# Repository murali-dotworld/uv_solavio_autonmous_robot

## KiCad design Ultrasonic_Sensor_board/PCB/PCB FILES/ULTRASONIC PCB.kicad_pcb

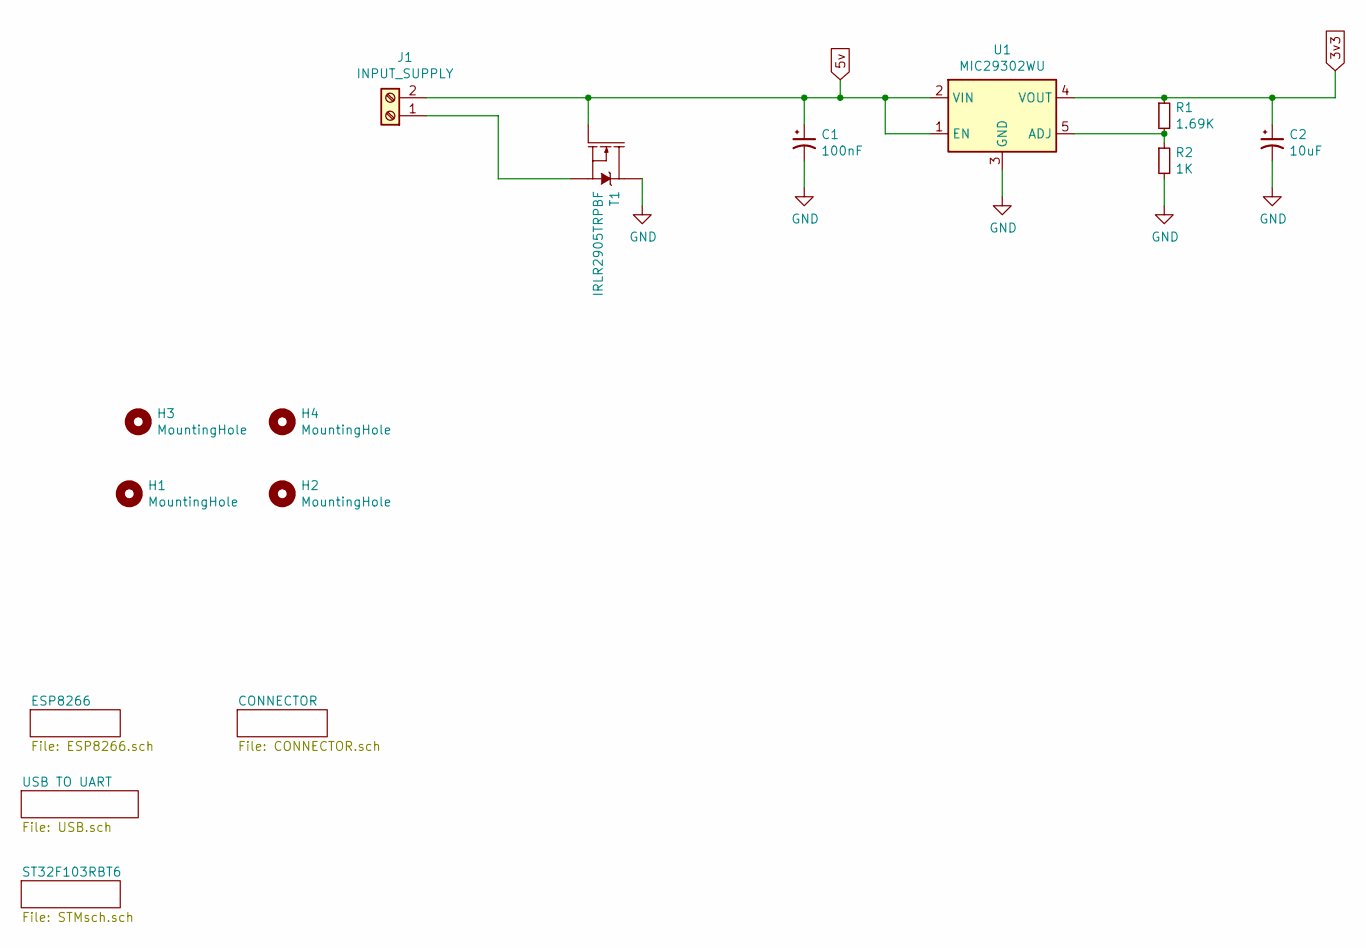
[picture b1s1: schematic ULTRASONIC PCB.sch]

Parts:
C1: 100nF; CP_Radial_D5.0mm_P2.00mm
C2: 10uF; CP_Radial_D5.0mm_P2.00mm
H1, H2, H3, H4: MountingHole; MountingHole_4.3mm_M4
J1: INPUT_SUPPLY; TerminalBlock_bornier-2_P5.08mm
R1: 1.69K; R_0805_2012Metric
R2: 1K; R_0805_2012Metric
T1: IRLR2905TRPBF; TO252-3
U1: MIC29302WU; TO-263-5_TabPin3

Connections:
3v3: C2.1, R1.1, U1.4 (VOUT); also elsewhere on the board
5v: C1.1, J1.2, T1.1, U1.1 (EN), U1.2 (VIN); also elsewhere on the board
GND: C1.2, C2.2, R2.2, T1.2, T1.PAD, U1.3 (GND); also elsewhere on the board
unnamed: J1.1, T1.3
unnamed: R1.2, R2.1, U1.5 (ADJ)

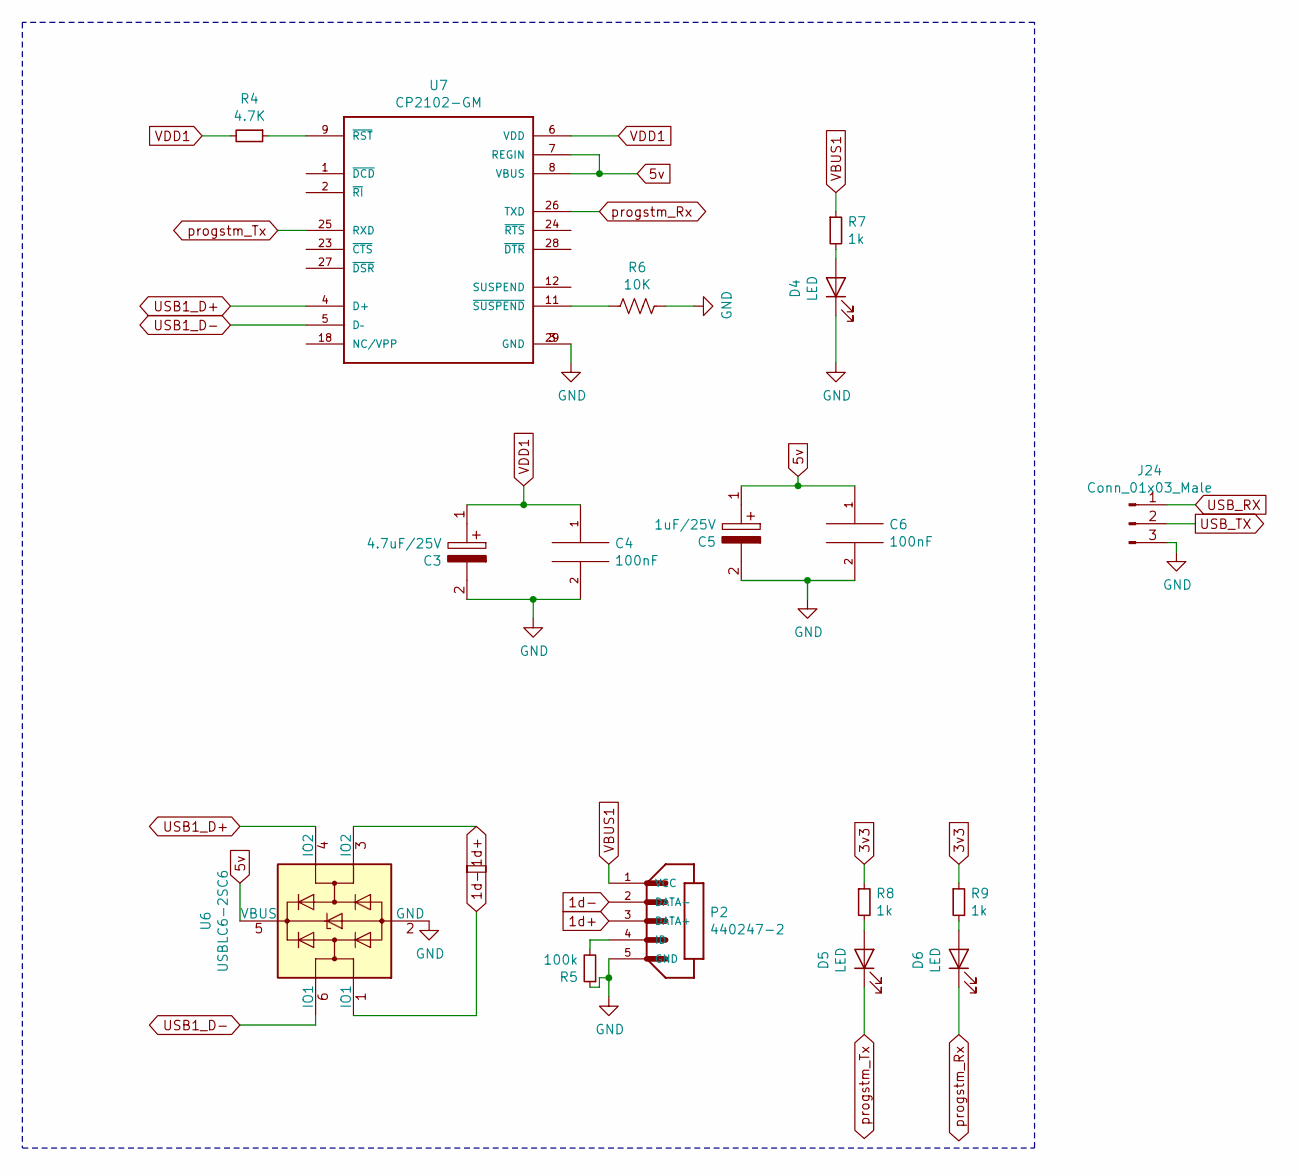
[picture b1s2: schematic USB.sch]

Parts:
C3: 4.7uF/25V; CP_EIA-3216-18_Kemet-A_Pad1.58x1.35mm_HandSolder; Manufacturer_Part_Number TAJA105M020RNJ; Mouser Part Number 581-TAJA105M020
C4, C6: 100nF; C_0805_2012Metric
C5: 1uF/25V; CP_EIA-3216-18_Kemet-A_Pad1.58x1.35mm_HandSolder; Manufacturer_Part_Number TAJA105M020RNJ; Mouser Part Number 581-TAJA105M020
D4, D5, D6: LED; LED_0805_2012Metric
J24: Conn_01x03_Male; PinHeader_1x03_P2.54mm_Vertical
P2: 440247-2; TE_440247-2
R4: 4.7K; R_0805_2012Metric
R5: 100k; R_0805_2012Metric
R6: 10K; R_0805_2012Metric
R7, R8, R9: 1k; R_0805_2012Metric
U6: USBLC6-2SC6; SOT-23-6
U7: CP2102-GM; QFN50P500X500X100-29N

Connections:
1d+: P2.3 (DATA+), U6.3 (IO2)
1d-: P2.2 (DATA-), U6.1 (IO1)
3v3: R8.1, R9.1; also elsewhere on the board
5v: C5.1, C6.1, U6.5 (VBUS), U7.7 (REGIN), U7.8 (VBUS); also elsewhere on the board
GND: C3.2, C4.2, C5.2, C6.2, D4.1 (K), J24.3, P2.5 (GND), R5.1, R6.1, U6.2 (GND), U7.3 (GND), U7.29 (GND); also elsewhere on the board
unnamed: D4.2 (A), R7.2
unnamed: D5.2 (A), R8.2
unnamed: D6.2 (A), R9.2
unnamed: P2.4 (ID), R5.2
unnamed: R4.1, U7.9 (~RST~)
unnamed: R6.2, U7.11 (~SUSPEND~)
USB1_D+: U6.4 (IO2), U7.4 (D+)
USB1_D-: U6.6 (IO1), U7.5 (D–)
USB_RX: J24.1; also elsewhere on the board
USB_TX: J24.2; also elsewhere on the board
VBUS1: P2.1 (VCC), R7.1
VDD1: C3.1, C4.1, R4.2, U7.6 (VDD)
progstm_Rx: D6.1 (K), U7.26 (TXD); also elsewhere on the board
progstm_Tx: D5.1 (K), U7.25 (RXD); also elsewhere on the board

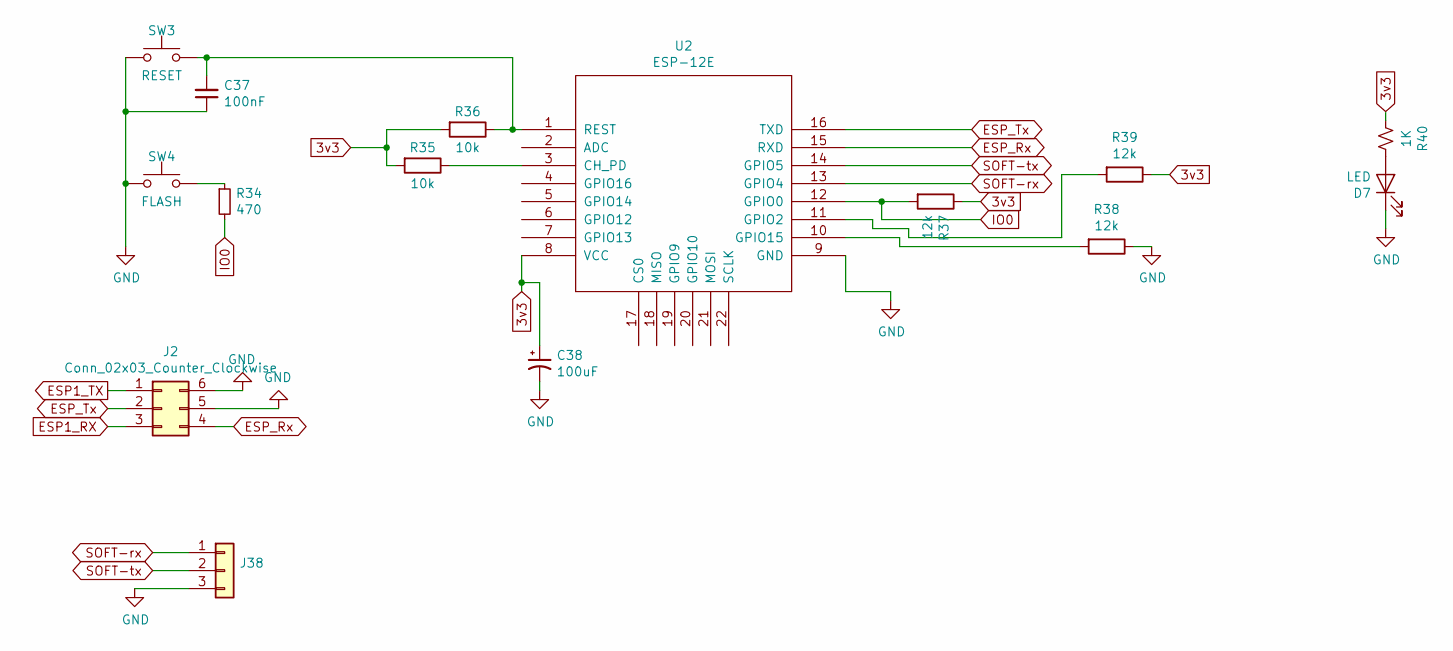
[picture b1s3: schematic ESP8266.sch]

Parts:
C37: 100nF; C_0805_2012Metric
C38: 100uF; CP_EIA-3216-18_Kemet-A_Pad1.58x1.35mm_HandSolder
D7: LED; LED_0805_2012Metric
J2: Conn_02x03_Counter_Clockwise; PinHeader_2x03_P2.54mm_Vertical
J38: Conn_01x03; PinHeader_1x03_P2.54mm_Vertical
R34: 470; R_0805_2012Metric
R35, R36: 10k; R_0805_2012Metric
R37, R38, R39: 12k; R_0805_2012Metric
R40: 1K; R_0805_2012Metric
SW3: RESET; SW_SPST_EVPBF
SW4: FLASH; SW_SPST_EVPBF
U2: ESP-12E; ESP-12E_SMD

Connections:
3v3: C38.1, R35.2, R36.2, R37.1, R39.1, R40.2, U2.8 (VCC); also elsewhere on the board
ESP1_RX: J2.3; also elsewhere on the board
ESP1_TX: J2.1; also elsewhere on the board
ESP_Rx: J2.4, U2.15 (RXD)
ESP_Tx: J2.2, U2.16 (TXD)
GND: C37.1, C38.2, D7.1 (K), J2.5, J2.6, J38.3, R38.1, SW3.1, SW4.1, U2.9 (GND); also elsewhere on the board
IO0: R34.2, R37.2, U2.12 (GPIO0)
unnamed: C37.2, R36.1, SW3.2, U2.1 (REST)
unnamed: D7.2 (A), R40.1
unnamed: R34.1, SW4.2
unnamed: R35.1, U2.3 (CH_PD)
unnamed: R38.2, U2.10 (GPIO15)
unnamed: R39.2, U2.11 (GPIO2)
SOFT-rx: J38.1, U2.13 (GPIO4)
SOFT-tx: J38.2, U2.14 (GPIO5)

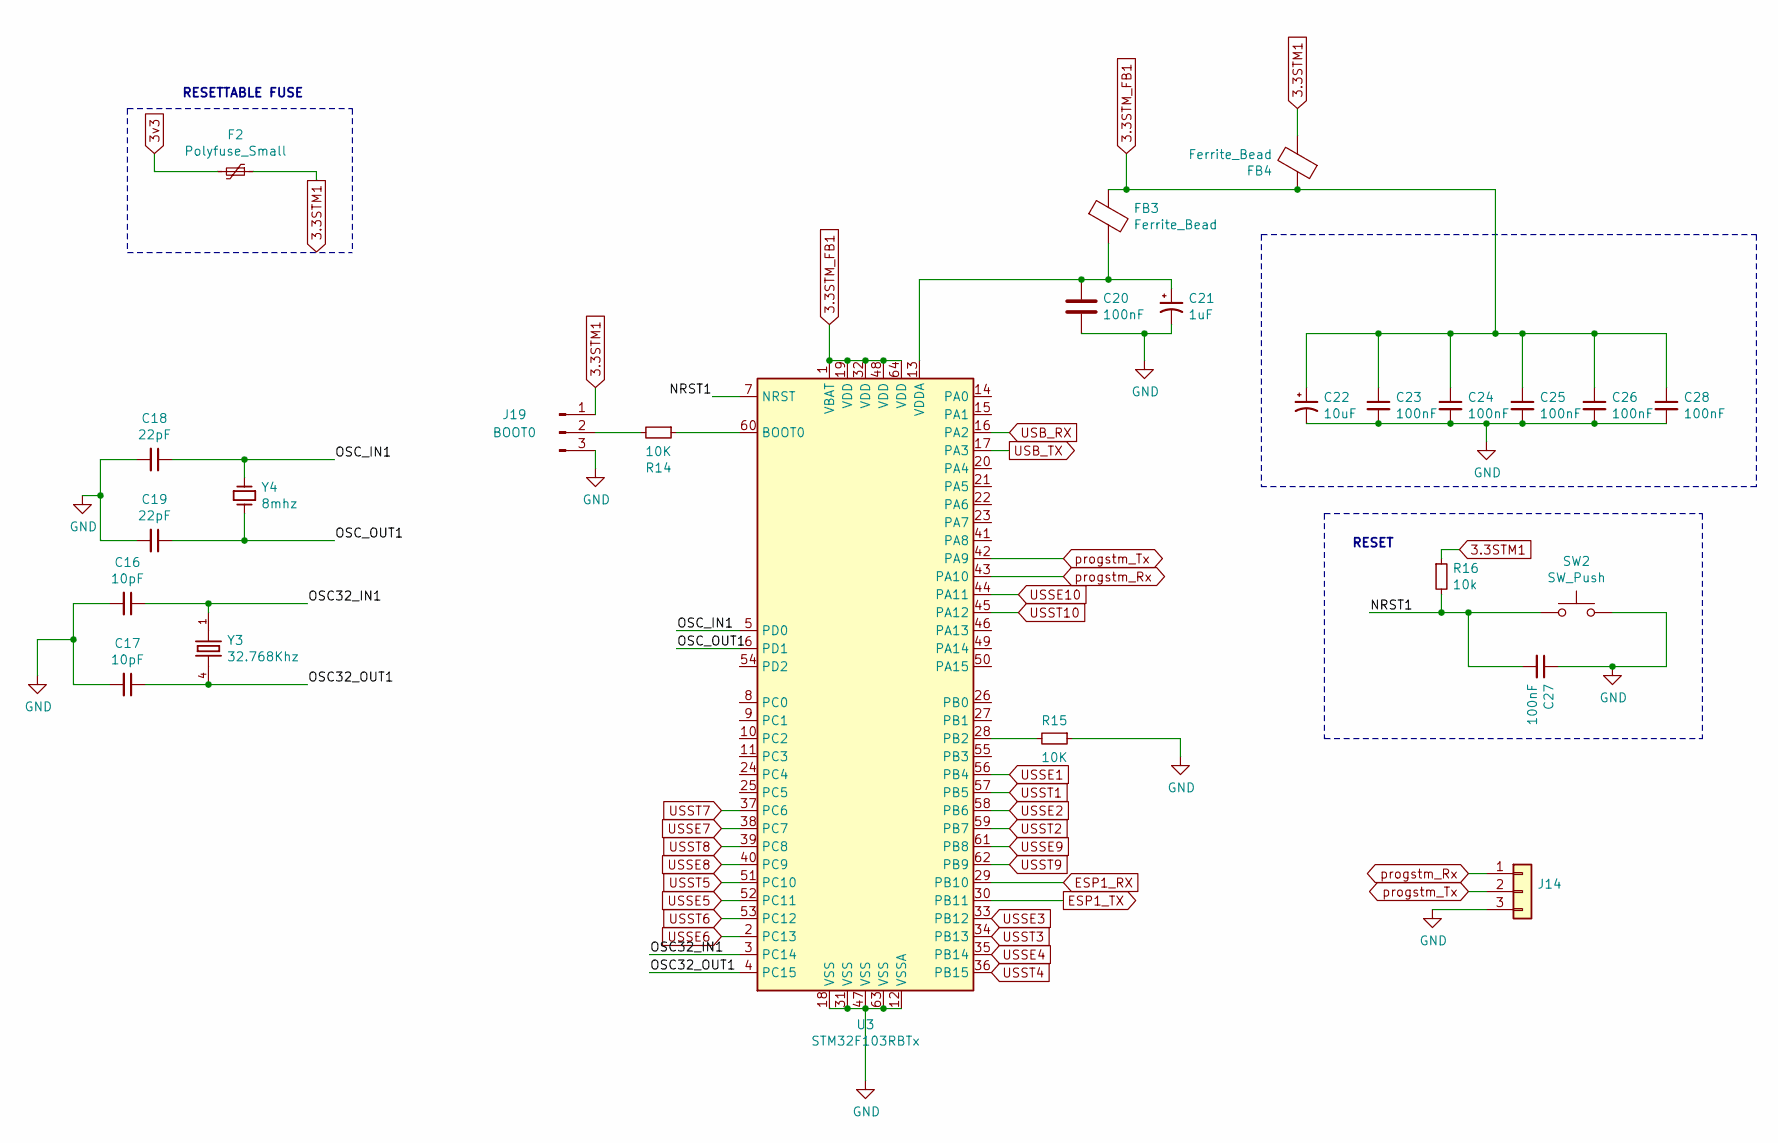
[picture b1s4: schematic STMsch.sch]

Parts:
C16, C17: 10pF; C_0805_2012Metric
C18, C19: 22pF; C_0805_2012Metric
C20, C23, C24, C25, C26, C27, C28: 100nF; C_0805_2012Metric
C21: 1uF; CP_EIA-3216-18_Kemet-A_Pad1.58x1.35mm_HandSolder
C22: 10uF; CP_EIA-3216-18_Kemet-A_Pad1.58x1.35mm_HandSolder
F2: Polyfuse_Small; C_1206_3216Metric
FB3, FB4: Ferrite_Bead; R_0805_2012Metric
J14: Conn_01x03; PinHeader_1x03_P2.54mm_Vertical
J19: BOOT0; PinHeader_1x03_P2.54mm_Vertical
R14, R15: 10K; R_0805_2012Metric
R16: 10k; R_0805_2012Metric
SW2: SW_Push; SW_SPST_EVPBF
U3: STM32F103RBTx; LQFP-64_10x10mm_P0.5mm
Y3: 32.768Khz; Crystal_SMD_SeikoEpson_MC306-4Pin_8.0x3.2mm
Y4: 8mhz; Crystal_HC49-U_Vertical

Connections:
3.3STM1: F2.1, FB4.2, J19.1, R16.1
3.3STM_FB1: C22.1, C23.1, C24.1, C25.1, C26.1, C28.1, FB3.1, FB4.1, U3.1 (VBAT), U3.19 (VDD), U3.32 (VDD), U3.48 (VDD), U3.64 (VDD)
3v3: F2.2; also elsewhere on the board
/ST32F103RBT6/NRST1: C27.2, R16.2, SW2.1, U3.7 (NRST)
/ST32F103RBT6/OSC32_IN1: C16.1, U3.3 (PC14), Y3.1
/ST32F103RBT6/OSC32_OUT1: C17.1, U3.4 (PC15), Y3.4
/ST32F103RBT6/OSC_IN1: C18.1, U3.5 (PD0), Y4.2
/ST32F103RBT6/OSC_OUT1: C19.1, U3.6 (PD1), Y4.1
ESP1_RX: U3.29 (PB10); also elsewhere on the board
ESP1_TX: U3.30 (PB11); also elsewhere on the board
GND: C16.2, C17.2, C18.2, C19.2, C20.2, C21.2, C22.2, C23.2, C24.2, C25.2, C26.2, C27.1, C28.2, J14.3, J19.3, R15.1, SW2.2, U3.12 (VSSA), U3.18 (VSS), U3.31 (VSS), U3.47 (VSS), U3.63 (VSS); also elsewhere on the board
unnamed: C20.1, C21.1, FB3.2, U3.13 (VDDA)
unnamed: J19.2, R14.2
unnamed: R14.1, U3.60 (BOOT0)
unnamed: R15.2, U3.28 (PB2)
USB_RX: U3.16 (PA2); also elsewhere on the board
USB_TX: U3.17 (PA3); also elsewhere on the board
USSE1: U3.56 (PB4); also elsewhere on the board
USSE2: U3.58 (PB6); also elsewhere on the board
USSE3: U3.33 (PB12); also elsewhere on the board
USSE4: U3.35 (PB14); also elsewhere on the board
USSE5: U3.52 (PC11); also elsewhere on the board
USSE6: U3.2 (PC13); also elsewhere on the board
USSE7: U3.38 (PC7); also elsewhere on the board
USSE8: U3.40 (PC9); also elsewhere on the board
USSE9: U3.61 (PB8); also elsewhere on the board
USSE10: U3.44 (PA11); also elsewhere on the board
USST1: U3.57 (PB5); also elsewhere on the board
USST2: U3.59 (PB7); also elsewhere on the board
USST3: U3.34 (PB13); also elsewhere on the board
USST4: U3.36 (PB15); also elsewhere on the board
USST5: U3.51 (PC10); also elsewhere on the board
USST6: U3.53 (PC12); also elsewhere on the board
USST7: U3.37 (PC6); also elsewhere on the board
USST8: U3.39 (PC8); also elsewhere on the board
USST9: U3.62 (PB9); also elsewhere on the board
USST10: U3.45 (PA12); also elsewhere on the board
progstm_Rx: J14.1, U3.43 (PA10); also elsewhere on the board
progstm_Tx: J14.2, U3.42 (PA9); also elsewhere on the board

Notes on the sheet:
RESETTABLE FUSE
RESET

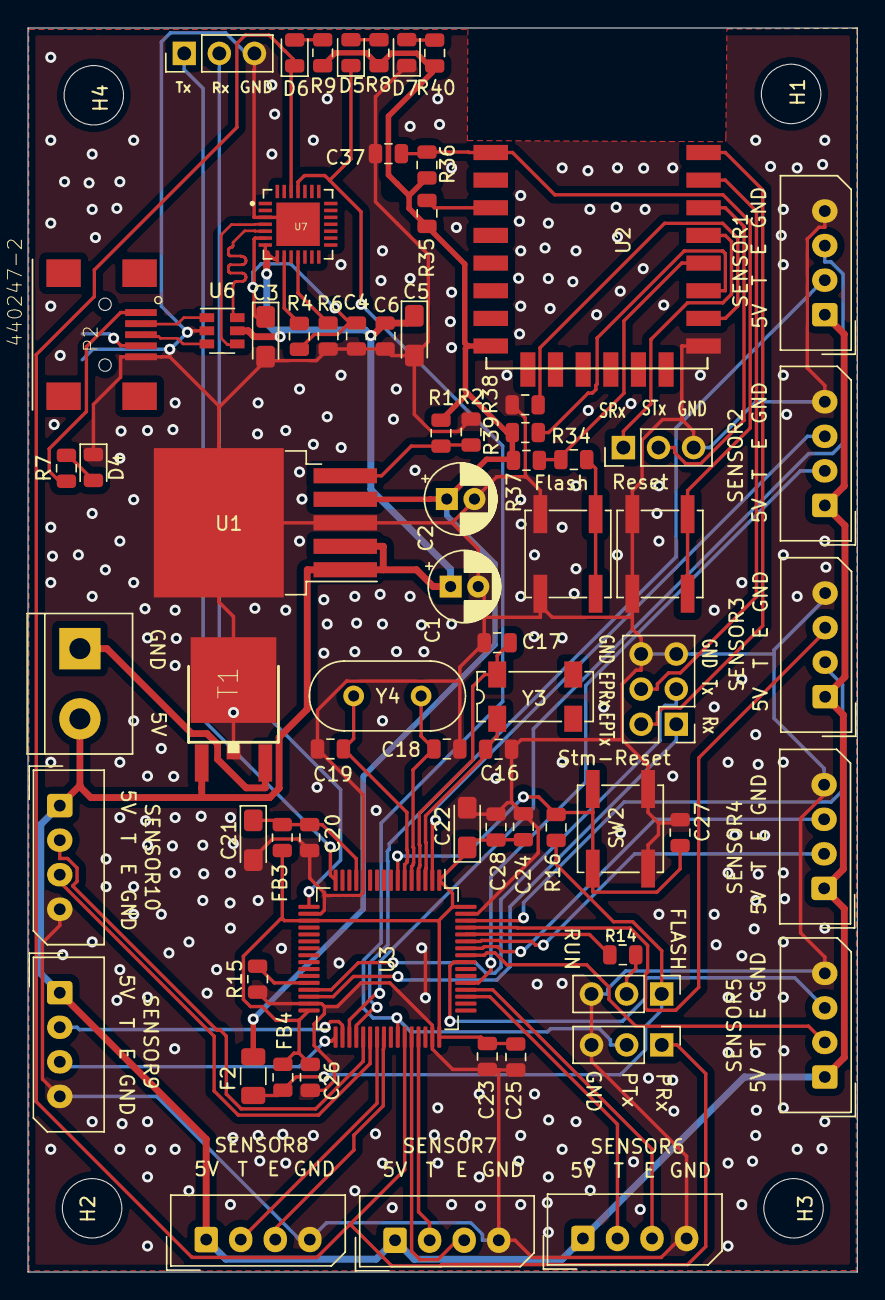
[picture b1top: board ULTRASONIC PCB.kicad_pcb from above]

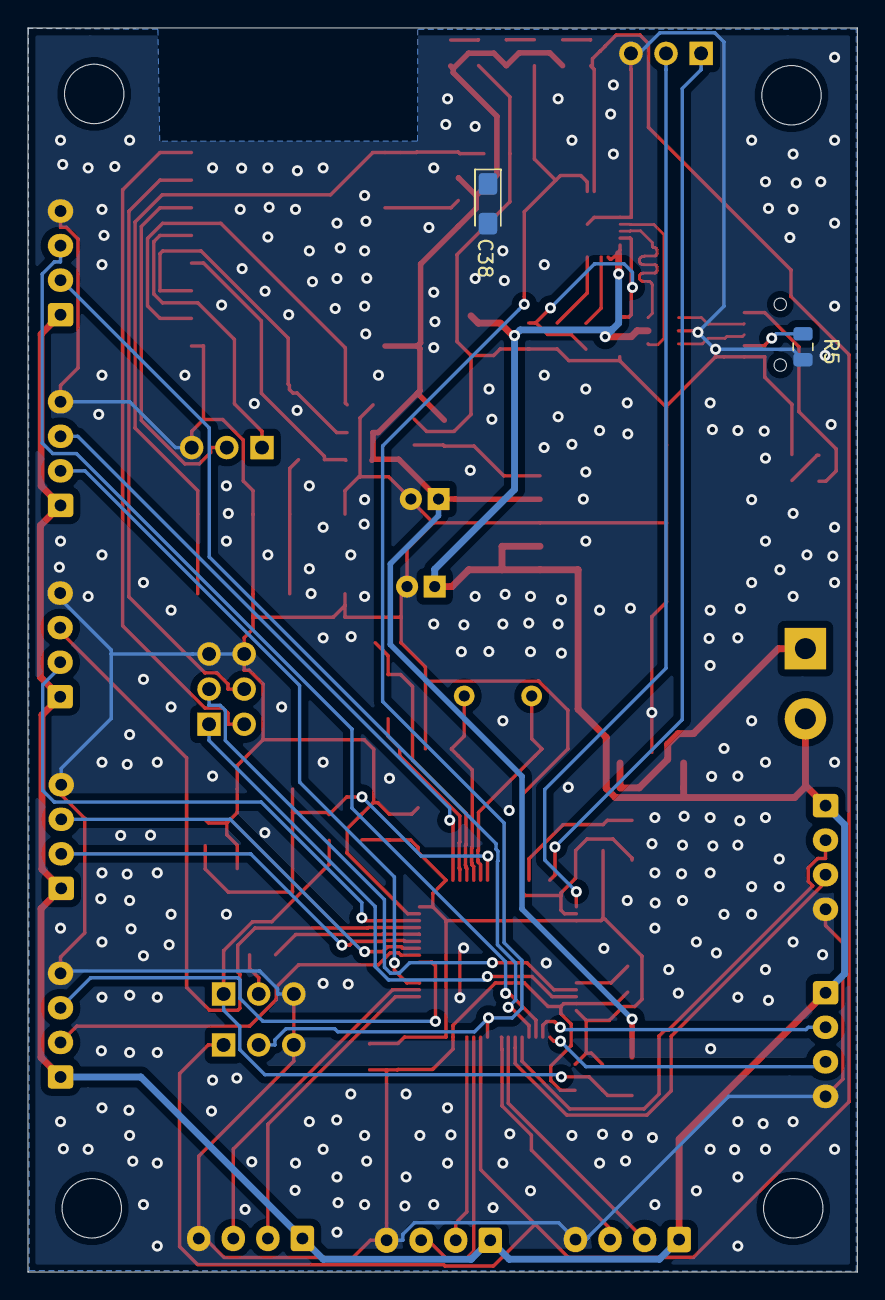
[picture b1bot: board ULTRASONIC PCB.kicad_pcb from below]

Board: 2 copper layers, 60.0 x 90.0 mm, 78 parts (2 on the bottom side), 65 nets.

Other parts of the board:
J3, J4, J5, J6, J7, J8, J9, J10, J11, J12: Screw_Terminal_01x04; Molex_SPOX_5267-04A_1x04_P2.50mm_Vertical

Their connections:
5v: J3.1, J4.1, J5.1, J6.1, J7.1, J8.1, J9.1, J10.1, J11.1, J12.1; also elsewhere on the board
GND: J3.4, J4.4, J5.4, J6.4, J7.4, J8.4, J9.4, J10.4, J11.4, J12.4; also elsewhere on the board
USSE1: J7.3; also elsewhere on the board
USSE2: J8.3; also elsewhere on the board
USSE3: J11.3; also elsewhere on the board
USSE4: J12.3; also elsewhere on the board
USSE5: J5.3; also elsewhere on the board
USSE6: J9.3; also elsewhere on the board
USSE7: J6.3; also elsewhere on the board
USSE8: J10.3; also elsewhere on the board
USSE9: J3.3; also elsewhere on the board
USSE10: J4.3; also elsewhere on the board
USST1: J7.2; also elsewhere on the board
USST2: J8.2; also elsewhere on the board
USST3: J11.2; also elsewhere on the board
USST4: J12.2; also elsewhere on the board
USST5: J5.2; also elsewhere on the board
USST6: J9.2; also elsewhere on the board
USST7: J6.2; also elsewhere on the board
USST8: J10.2; also elsewhere on the board
USST9: J3.2; also elsewhere on the board
USST10: J4.2; also elsewhere on the board

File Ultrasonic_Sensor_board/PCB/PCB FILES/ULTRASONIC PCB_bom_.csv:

Component,Description,Part,References,Value,Footprint,Quantity Per PCB,Datasheet,Mouser Price/Stock,Mouser Part Number,Manufacturer_Name,Height,RS Price/Stock,RS Part Number,Manufacturer_Part_Number,Field10,Field8,Field9,Field4,Field7,Field6,Field5
1,"Unpolarized capacitor, small symbol",C_Small,C16 C17,10pF,C_0805_2012Metric,2,~,,,,,,,,,,,,,,
2,"Unpolarized capacitor, small symbol",C_Small,C18 C19,22pF,C_0805_2012Metric,2,~,,,,,,,,,,,,,,
3,"Polarized capacitor, small US symbol",CP1_Small,C1,100nF,CP_Radial_D5.0mm_P2.00mm,1,~,,,,,,,,,,,,,,
4,Unpolarized capacitor,C,C20 C23 C24 C25 C26 C27 C28 C37,100nF,C_0805_2012Metric,8,~,,,,,,,,,,,,,,
5,Capacitor symbol for simulation only,C,C4 C6,100nF,C_0805_2012Metric,2,~,,,,,,,,,,,,,,
6,"Polarized capacitor, small US symbol",CP1_Small,C21,1uF,CP_EIA-3216-18_Kemet-A_Pad1.58x1.35mm_HandSolder,1,~,,,,,,,,,,,,,,
7,"Polarized capacitor, small US symbol",CP1_Small,C2,10uF,CP_Radial_D5.0mm_P2.00mm,1,~,,,,,,,,,,,,,,
8,"Polarized capacitor, small US symbol",CP1_Small,C22,10uF,CP_EIA-3216-18_Kemet-A_Pad1.58x1.35mm_HandSolder,1,~,,,,,,,,,,,,,,
9,"Polarized capacitor, small US symbol",CP1_Small,C38,100uF,CP_EIA-3216-18_Kemet-A_Pad1.58x1.35mm_HandSolder,1,~,,,,,,,,,,,,,,
10,,TAJA105M020RNJ-c1206_smd_tantalum-Door_Locking-rescue,C5,1uF/25V,CP_EIA-3216-18_Kemet-A_Pad1.58x1.35mm_HandSolder,1,http://www.farnell.com/datasheets/1680476.pdf,https://www.mouser.com/Search/Refine.aspx?Keyword=581-TAJA105M020,581-TAJA105M020,AVX,1.8,http://uk.rs-online.com/web/p/products/1360152,1360152,TAJA105M020RNJ,,,,,,,
11,,TAJA105M020RNJ-c1206_smd_tantalum-Door_Locking-rescue,C3,4.7uF/25V,CP_EIA-3216-18_Kemet-A_Pad1.58x1.35mm_HandSolder,1,http://www.farnell.com/datasheets/1680476.pdf,https://www.mouser.com/Search/Refine.aspx?Keyword=581-TAJA105M020,581-TAJA105M020,AVX,1.8,http://uk.rs-online.com/web/p/products/1360152,1360152,TAJA105M020RNJ,,,,,,,
12,Light emitting diode,LED,D4 D5 D6 D7,LED,LED_0805_2012Metric,4,~,,,,,,,,,,,,,,
13,"Resettable fuse, polymeric positive temperature coefficient, small symbol",Polyfuse_Small,F2,Polyfuse_Small,C_1206_3216Metric,1,~,,,,,,,,,,,,,,
14,Ferrite bead,Ferrite_Bead,FB3 FB4,Ferrite_Bead,R_0805_2012Metric,2,~,,,,,,,,,,,,,,
15,"Generic connector, single row, 01x03, script generated (kicad-library-utils/schlib/autogen/connector/)",Conn_01x03_Male,J19 J24,BOOT0,PinHeader_1x03_P2.54mm_Vertical,2,~,,,,,,,,,,,,,,
16,"Generic connector, single row, 01x03, script generated (kicad-library-utils/schlib/autogen/connector/)",Conn_01x03,J14 J38,Conn_01x03,PinHeader_1x03_P2.54mm_Vertical,2,~,,,,,,,,,,,,,,
17,"Generic connector, double row, 02x03, counter clockwise pin numbering scheme (similar to DIP packge numbering), script generated (kicad-library-utils/schlib/autogen/connector/)",Conn_02x03_Counter_Clockwise,J2,Conn_02x03_Counter_Clockwise,PinHeader_2x03_P2.54mm_Vertical,1,~,,,,,,,,,,,,,,
18,"Generic screw terminal, single row, 01x02, script generated (kicad-library-utils/schlib/autogen/connector/)",Screw_Terminal_01x02,J1,INPUT_SUPPLY,TerminalBlock_bornier-2_P5.08mm,1,~,,,,,,,,,,,,,,
19,"Generic screw terminal, single row, 01x04, script generated (kicad-library-utils/schlib/autogen/connector/)",Screw_Terminal_01x04,J3 J4 J5 J6 J7 J8 J9 J10 J11 J12,Screw_Terminal_01x04,Molex_SPOX_5267-04A_1x04_P2.50mm_Vertical,10,~,,,,,,,,,,,,,,
20,,440247-2-USB_MINI_B-SNAPEDA-Door_Locking-rescue,P2,440247-2,TE_440247-2,1,TE Connectivity,,,,,,,,https://www.te.com/usa-en/product-440247-2.html?te_bu=Cor&te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,440247-2,None,None,Mini USB B Type RCPT,Unavailable,440247-2
21,"Resistor, small symbol",R_Small,R34,470,R_0805_2012Metric,1,~,,,,,,,,,,,,,,
22,"Resistor, small symbol",R_Small,R2 R7 R8 R9,1K,R_0805_2012Metric,4,~,,,,,,,,,,,,,,
23,,R_Small_US-Device-esp-max-rescue,R40,1K,R_0805_2012Metric,1,~,,,,,,,,,,,,,,
24,"Resistor, small symbol",R_Small,R1,1.69K,R_0805_2012Metric,1,~,,,,,,,,,,,,,,
25,"Resistor, small symbol",R_Small,R4,4.7K,R_0805_2012Metric,1,~,,,,,,,,,,,,,,
26,"Resistor, small symbol",R_Small,R14 R15 R16 R35 R36,10K,R_0805_2012Metric,5,~,,,,,,,,,,,,,,
27,"Resistor, US symbol",R_US,R6,10K,R_0805_2012Metric,1,~,,,,,,,,,,,,,,
28,Resistor,R,R37 R38 R39,12k,R_0805_2012Metric,3,~,,,,,,,,,,,,,,
29,"Resistor, small symbol",R_Small,R5,100k,R_0805_2012Metric,1,~,,,,,,,,,,,,,,
30,"Push button switch, generic, two pins",SW_Push,SW4,FLASH,SW_SPST_EVPBF,1,~,,,,,,,,,,,,,,
31,"Push button switch, generic, two pins",SW_Push,SW3,RESET,SW_SPST_EVPBF,1,~,,,,,,,,,,,,,,
32,"Push button switch, generic, two pins",SW_Push,SW2,SW_Push,SW_SPST_EVPBF,1,~,,,,,,,,,,,,,,
33,,IRLR2905TRPBF,T1,IRLR2905TRPBF,TO252-3,1,Infineon Technologies,,,,,,,,,,,,,,
34,,CP2102-GM-CP2102-GM-Door_Locking-rescue,U7,CP2102-GM,QFN50P500X500X100-29N,1,Silicon Labs,,,,,,,,,QFN-28 Silicon Labs,,336-1160-5-ND,CP2102-GM,https://www.digikey.in/product-detail/en/silicon-labs/CP2102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,Microcontroller Solutions - Interface Products USB to UART Bdg Chip
35,"ESP8266 ESP-12E module, 22 pins, 2mm, PCB antenna",ESP-12E,U2,ESP-12E,ESP-12E_SMD,1,http://l0l.org.uk/2014/12/esp8266-modules-hardware-guide-got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,,,,,,,,,,,,,,
36,"3A low dropout linear regulator, adjustable output, TO-263",MIC29302WU,U1,MIC29302WU,TO-263-5_TabPin3,1,http://ww1.microchip.com/downloads/en/devicedoc/20005685a.pdf,,,,,,,,,,,,,,
37,"ARM Cortex-M3 MCU, 128KB flash, 20KB RAM, 72MHz, 2-3.6V, 51 GPIO, LQFP-64",STM32F103RBTx,U3,STM32F103RBTx,LQFP-64_10x10mm_P0.5mm,1,http://www.st.com/st-web-ui/static/active/en/resource/techni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,,,,,,,,,,,,,,
38,"Bidirectional ESD Protection Diode, SOT-23-6",USBLC6-2SC6,U6,USBLC6-2SC6,SOT-23-6,1,http://www2.st.com/resource/en/datasheet/CD00050750.pdf,,,,,,,,,,,,,,
39,,MC-306_32.7680K-A5__ROHS-32.768KHz_crystals_smd-Door_Locking-rescue,Y3,32.768Khz,Crystal_SMD_SeikoEpson_MC306-4Pin_8.0x3.2mm,1,MC-306 32.7680K-A5: ROHS,,,,,,,,,Crystal 32.7680 Khz 12.5pf Smd,,EPSON,Unavailable,None,4-4 Epson
40,,LFXTAL003237-8MHz_smd_crystal-Door_Locking-rescue,Y4,8mhz,Crystal_HC49-U_Vertical,1,Unavailable,,,,,,,,,LFXTAL003237,,HC49/4HSMX Series 16.000 MHz ±30 ppm 16 pF Low Profile Surface Mount Crystal,None,IQD Frequency Products,HC-49/US IQD Frequency Products





Component Groups:,40
Component Count:,74
Fitted Components:,74
Number of PCBs:,1
Total components:,74
Schematic Version:,
Schematic Date:,
PCB Variant:,[u'default']
BoM Date:,11/27/2020 7:10:34 PM
Schematic Source:,ULTRASONIC PCB.sch
KiCad Version:,Eeschema (5.1.5)-3

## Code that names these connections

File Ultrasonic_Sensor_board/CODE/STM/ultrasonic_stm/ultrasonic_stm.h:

#include <ArduinoJson.h>

/*#define*/
#define no_of_sensor 7
#define serial_baud_rate 115200
#define esp_baud_rate 115200
#define esp_serial Serial2
#define stm_serial Serial

/*Variable Declaration*/
int USSE[] = {PB14, PC13, PB8, PB6, PB4, PC9, PA11, PC10,PB12,PC7}; //Echo pin for ultrasonic sensor
int USST[] = {PB15, PC12, PB9, PB7, PB5, PC8, PA12, PC11,PB13,PC6}; //Trigger pin for ultrasonic sensor
long duration[7], distance[7];
int mac_set = 0;
uint16_t timeout_sensor = 31000;
int first_time = 0;
float speed_of_sound = 29.1;
int divide = 2;
int delay_millisecond = 10;
int absolute_zero = 0;
int not_mac_set = 0;
const byte MaxByteArraySize = 6;
byte byteArray[MaxByteArraySize] = {0};
int ONE = 1;

/*JSON Document*/
StaticJsonDocument<1024> root;
StaticJsonDocument<1024> send_data;

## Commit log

2021-04-10 Added the code for uv_solavia_autonmous_robot
